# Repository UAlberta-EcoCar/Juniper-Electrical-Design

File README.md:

# Juniper-Electrical-Design - Wiper Board

The Wiper Board drives the windshield wiper on Juniper, the 2026-2027 EcoCar Urban Concept car. Shell Eco-marathon rules (2027 Chapter I, Art. 52) require Urban Concept cars to run in light rain, with an electric wiper like a production car's, worked by its own switch within easy reach of the driver. The board runs a 12 V self-parking wiper motor, reads the driver's dash switch and the park sensors, and reports its status over CAN FD. This branch contains the Rev1 board as built, the Rev2 schematic in progress, and the STM32 firmware.

Board Requirements:

- Drive a 12 V wiper motor (about 30 W) with a hardware current limit (set to about 3.5 A)
- Dedicated driver wiper switch input (off / slow / fast) on a harness connector
- Hall-sensor inputs for wiper park and end-of-sweep detection
- Reverse-polarity and transient protection on the 12 V input
- CAN FD for commands and status
- RGB status LEDs (WS2812B) and an optional OLED debug display
- USB-C and SWD for programming and debugging
- Low idle power, since all electrical energy counts on the joulemeter

MCU Chosen: STM32G491KEU6 (UFQFPN32)

- Chosen for its FDCAN controller, timers and ADCs in a small package, and the team's experience with the STM32G4 family.

Motor Driver: STMicroelectronics STSPIN948 (VFQFPN48)

- Dual full-bridge, 4.5 A rms per bridge, up to 58 V, with built-in current-sense amplifiers, an adjustable current limiter and overcurrent, thermal and undervoltage protection. The design follows ST's [EVSPIN948](https://www.st.com/en/evaluation-tools/evspin948.html) evaluation board. Bridge A drives the wiper motor; bridge B is a spare.

# Repository Structure

| Folder | Contents |
|---|---|
| `Hardware/Rev1/` | Rev1 board as built: KiCad 9 schematic, PCB, BOM and production files |
| `Hardware/Rev2/` | Rev2 schematic (work in progress) |
| `firmware/` | STM32CubeIDE project and CubeMX configuration (`Wiper-Board-Firmwire.ioc`); Rev2 configuration in `v2Firmwire/` |

# Getting Started

Clone the repository:

```sh
git clone --recursive https://github.com/UAlberta-EcoCar/Juniper-Electrical-Design.git
```

Switch to this branch:

```sh
git checkout Wiper-Board
```

Open `Hardware/Rev2/defogger_and_wiper.kicad_pro` in KiCad 9. The schematic uses a 25 mil grid; set the connection grid and the wire grid override to 25 mil.

Open `firmware/` as an existing project in STM32CubeIDE to build and flash the firmware.

# Rev2 Pin Map

| Pin | Function |
|---|---|
| PA6 / PA7 | PWM1A / PWM1B to the driver (TIM16_CH1 / TIM17_CH1) |
| PA8 / PA9 | PHA / PHB (direction) |
| PB4 / PB3 | EN/nFAULT A / B (open-drain, 39 k pull-up) |
| PA10 | nSTBY (100 k pull-down: driver sleeps until firmware wakes it) |
| PA3 / PB0 | Motor current A / B (0.5 V/A) |
| PA4 / PA5 | Wiper switch inputs BTN1 / BTN2 (dash connector J9 and on-board buttons) |
| PA0 / PA2 | Hall park sensors (J7) |
| PB5 / PB6 | FDCAN2 RX / TX |
| PA15 / PB7 | I2C1 SCL / SDA (OLED) |
| PB8 | WS2812B data (TIM8_CH2, via 74AHCT1G125; 10 k pull-down keeps BOOT0 low) |
| PA11 / PA12 | USB |
| PA13 / PA14 | SWD |
| PF0 | 8 MHz oscillator input (HSE bypass) |

# Bring-up Notes

- Driver mode switches MODE1 / MODE2 / MODE3 = LOW / HIGH / LOW (dual independent full-bridge). Power-cycle after any change.
- Rev1 only: SCL sits on PB8 (BOOT0), so the board boots into the ST bootloader after a power cycle. Program option bytes nSWBOOT0 = 0 and nBOOT0 = 1, or run it with the debugger attached. Fixed in Rev2.
- Rev1 only: the REF dividers (5.6 k / 1 k) limit the motor to about 1 A. Rev2 uses 910 ohm (about 3.5 A).

# Status

- [x] Rev1 board built and brought up
- [ ] Rev2 schematic
- [ ] Rev2 PCB layout
- [ ] Rev2 firmware

Onboarding documentation here: [https://ualberta-ecocar.github.io/Documentation/](https://ualberta-ecocar.github.io/Documentation/)

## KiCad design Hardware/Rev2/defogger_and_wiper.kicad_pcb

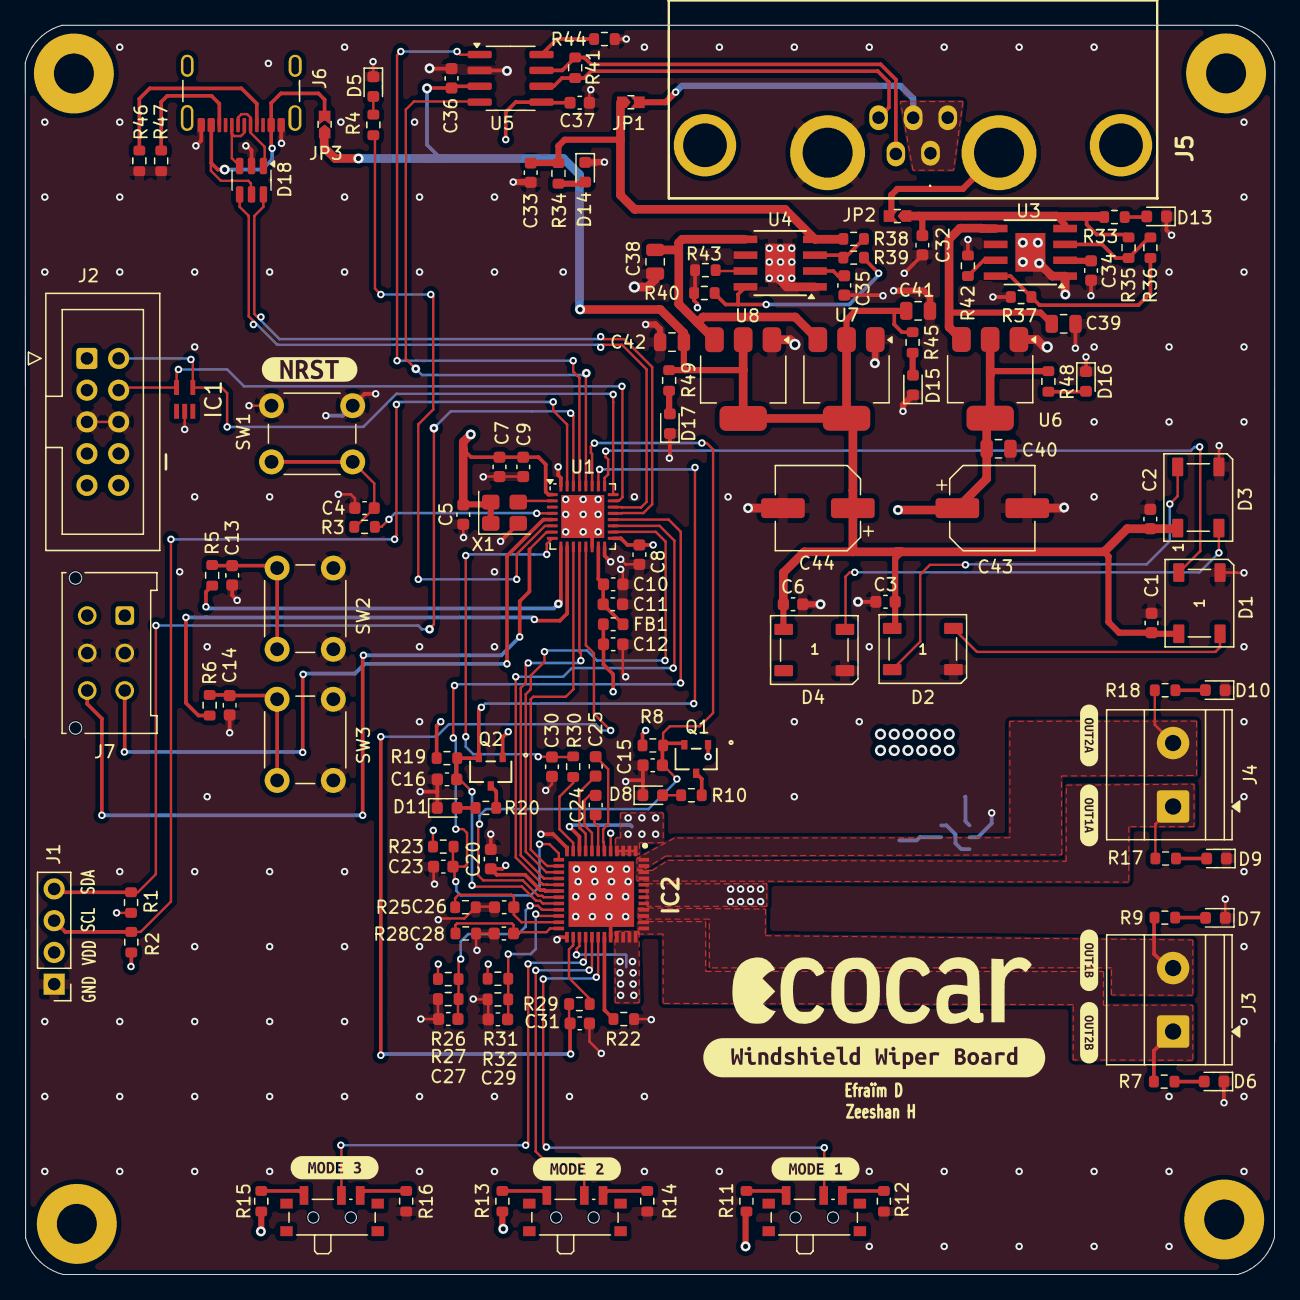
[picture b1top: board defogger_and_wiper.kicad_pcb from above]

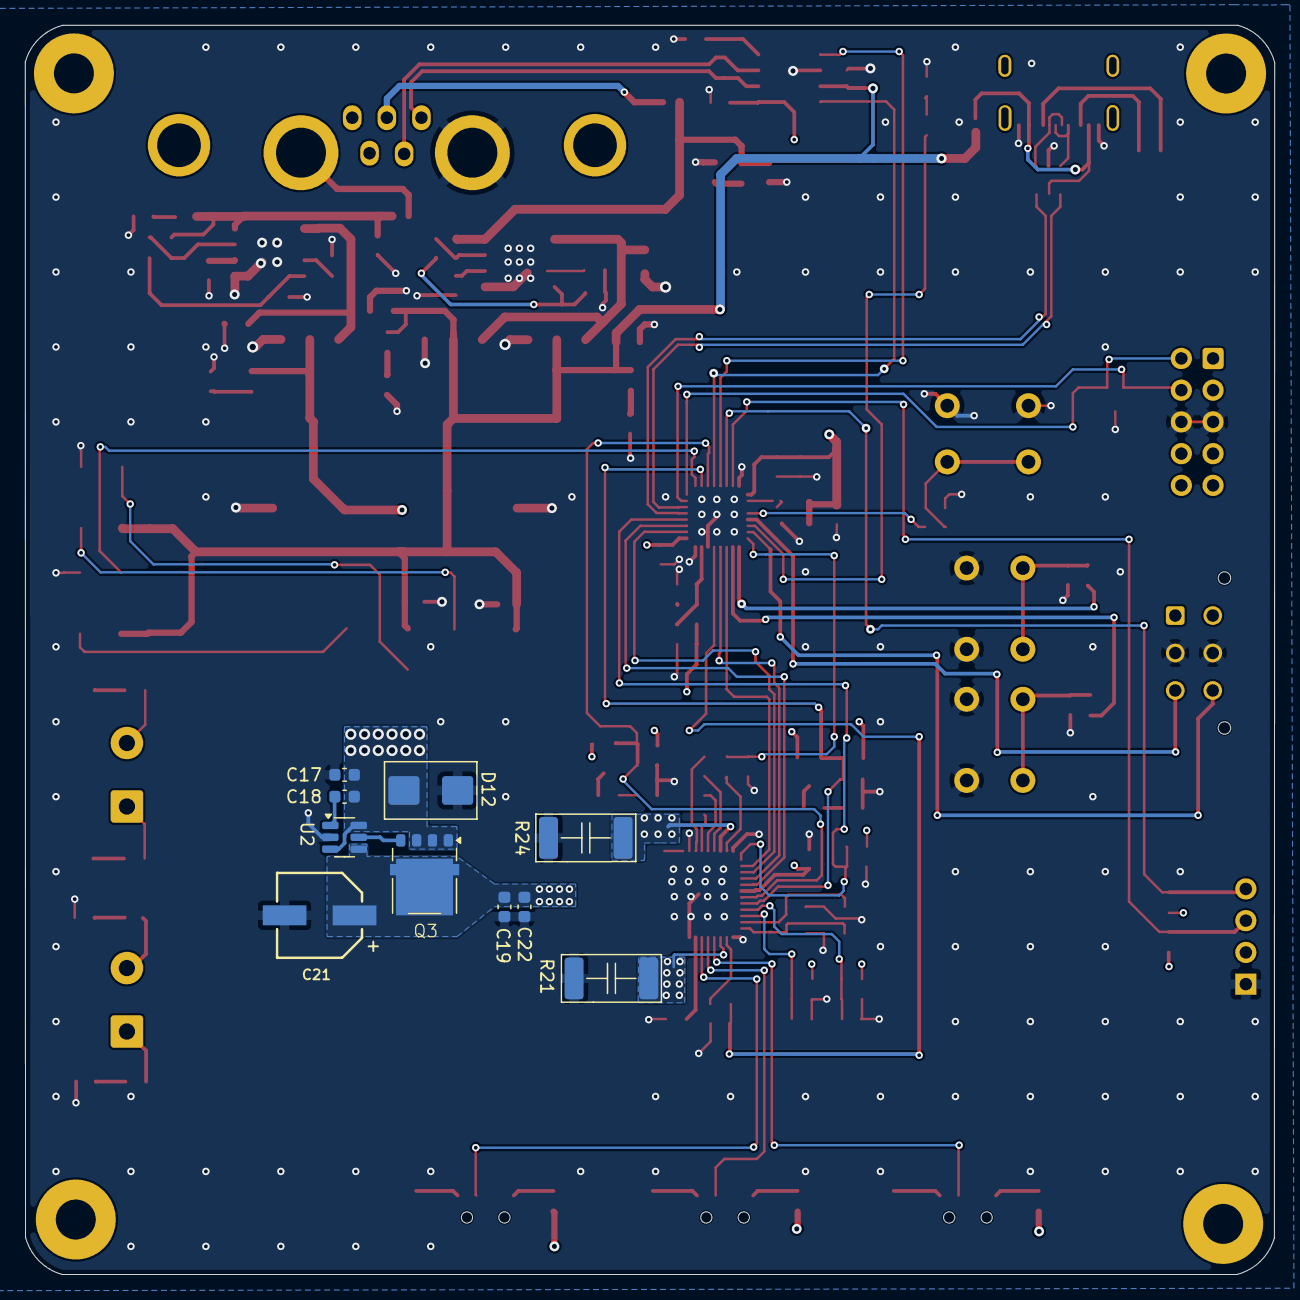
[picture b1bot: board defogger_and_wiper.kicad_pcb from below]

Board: 4 copper layers, 100.0 x 100.0 mm, 155 parts (10 on the bottom side), 100 nets.

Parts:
C1, C2, C3, C6, C10, C15, C16: 10n; C_0603_1608Metric
C4, C5, C8, C9, C13, C14, C24, C27, C29, C32, C33, C36, C37: 100n; C_0603_1608Metric
C7: 4u7; C_0603_1608Metric
C11, C12, C25: 1u; C_0603_1608Metric
C17, C19, C22: 22n; C_0603_1608Metric
C18: 0.1uF; C_0603_1608Metric
C20: 220n; C_0603_1608Metric
C21: 47u; WCAP-ASLI_6.3X5.5_DXL_
C23, C26, C28: 1n; C_0603_1608Metric
C30, C31: 100p; C_0603_1608Metric
C34, C35: 2n2; C_0603_1608Metric
C38, C39, C40, C41, C42: 10u; C_0805_2012Metric
C43, C44: 100u; CP_Elec_6.3x9.9
D1, D2, D3, D4: WS2812B; LED_WS2812B_PLCC4_5.0x5.0mm_P3.2mm
D5: GREEN; LED_0603_1608Metric
D6, D7, D9, D10, D13, D14, D15, D16, D17: BLUE; LED_0603_1608Metric
D8, D11: RED; LED_0603_1608Metric
D12: SMBJ33CA; D_SMB_TVS
D18: USBLC6-2SC6; TSOT-23-6
FB1: 600@100MHz 1A; L_0603_1608Metric
H1, H2, H3, H4: MountingHole; MountingHole_3.2mm_M3_Pad
IC1: ESDALC6V1W5; SOT65P210X110-5N
IC2: STSPIN948; QFN50P700X700X105-49N-D
J1: OLED; Display_128x64_096_I2C
J2: STM32-Prog-Header; IDC-STM32-Prog-Header_2x05_P2.54mm_Vertical
J3: MotorConnB; TerminalBlock_Phoenix_MKDS-1,5-2-5.08_1x02_P5.08mm_Horizont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
J4: MotorConnA; TerminalBlock_Phoenix_MKDS-1,5-2-5.08_1x02_P5.08mm_Horizont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
J5: Male Conn; DB7W2-Male
J6: USBC; USB_C_Receptacle_GCT_USB4105-xx-A_16P_TopMnt_Horizontal
J7: Molex_6_Pin; Molex_6_Pin_FTP
JP1: 12V Buck; J_0603_Triangular
JP2: 7V Buck; J_0603_Triangular
JP3: VBUS; J_0603_Triangular
MODE1, MODE2, MODE3: SW_SPDT; SW_SPDT_PCM12
Q1, Q2: PMOS; SOT-23_TO-236_318-AT_OSI
Q3: NTMFS4D0N08XT1G; PowerMosDFNHybrid
R1: 4k7; R_0603_1608Metric
R2: 4K7; R_0603_1608Metric
R3, R7, R9, R11, R12, R13, R14, R15, R16, R17, R18, R44: 10K; R_0603_1608Metric
R4, R36, R39, R40, R45, R48, R49: 1k; R_0603_1608Metric
R5, R6, R38: 10k; R_0603_1608Metric
R8, R19: 39K; R_0603_1608Metric
R10, R20: 330; R_0603_1608Metric
R21, R24: 50m; C_2512_6332Metric_Pad1.52x3.35mm_HandSolder
R22: 5.6K; R_0603_1608Metric
R23: 18k; R_0603_1608Metric
R25, R28: 22k; R_0603_1608Metric
R26, R31: 5.6k; R_0603_1608Metric
R27, R32: 1K; R_0603_1608Metric
R29, R30: 100; R_0603_1608Metric
R33, R34: 2k; R_0603_1608Metric
R35: 8k2; R_0603_1608Metric
R37: 1k2; R_0603_1608Metric
R41: 120R; R_0603_1608Metric
R42: 680R; R_0603_1608Metric
R43: 470R; R_0603_1608Metric
R46, R47: 5.1k; R_0603_1608Metric
SW1: RESET; SW_PUSH_6mm_H5mm
SW2: BTN1; SW_PUSH_6mm_H5mm
SW3: BTN2; SW_PUSH_6mm_H5mm
U1: STM32G491KEU6; QFN-32-1EP_5x5mm_P0.5mm_EP3.45x3.45mm
U2: LM74700; SOT-23-6
U3, U4: TPS2596; TI_SO-PowerPAD-8
U5: MCP2542FD-E/SN; SOIC-8_3.9x4.9mm_P1.27mm
U6: AZ1117IH-3.3; SOT-223-3_TabPin2
U7, U8: AZ1117-5.0; SOT-223-3_TabPin2
X1: 8Mhz; Crystal_SMD_3225-4Pin_3.2x2.5mm
kibuzzard-6A239A28: G***; kibuzzard-6A239A28
kibuzzard-6A239A38: G***; kibuzzard-6A239A38
kibuzzard-6A239A81: G***; kibuzzard-6A239A81
kibuzzard-6A239AAD: G***; kibuzzard-6A239AAD
kibuzzard-6A239ABD: G***; kibuzzard-6A239ABD
kibuzzard-6A2398C4: G***; kibuzzard-6A2398C4
kibuzzard-6A2399CD: G***; kibuzzard-6A2399CD
kibuzzard-6A2399E7: G***; kibuzzard-6A2399E7
kibuzzard-696D2580: G***; kibuzzard-696D2580

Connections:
+3.3VA: C10.1, C11.1, FB1.2, U1.15 (VDDA)
+3V3: C5.1, C7.1, C8.1, C9.1, C12.1, C20.1, C37.2, C40.1, C43.1, FB1.1, IC2.18 (VDD), J1.2, J2.7 (3.3V), J2.8 (3.3V), J7.1, J7.4, Q1.1 (D), Q2.1 (D), R1.1, R2.1, R8.1, R11.1, R13.1, R15.1, R19.1, R23.1, R26.1, R31.1, R48.1, U1.1 (VDD), U1.17 (VDD), U5.5 (VIO), U6.2 (VO), X1.1 (Tri-State), X1.4 (VDD)
+5V: C1.1, C2.1, C3.1, C6.1, C36.2, C41.1, C42.1, C44.1, D1.1 (VDD), D2.1 (VDD), D3.1 (VDD), D4.1 (VDD), JP3.1 (A), R45.1, R49.1, U5.3 (VDD), U7.2 (VO), U8.2 (VO)
+12V: C38.1, U4.5 (OUT), U7.3 (VI), U8.3 (VI)
/ADC_VA: C30.1, R30.1, U1.8 (PA3)
/ADC_VB: C31.1, R29.1, U1.13 (PB0)
/BTN1: R5.1, U1.9 (PA4)
/BTN2: R6.1, U1.10 (PA5)
/CAN AND POWER/CAN+: J5.2, R41.1, U5.7 (CANH)
/CAN AND POWER/CAN-: J5.5, R41.2, U5.6 (CANL)
/CAN AND POWER/FUSE1_IN: C33.1, JP1.1 (A), R34.1, R38.2, U4.4 (IN)
/CAN AND POWER/FUSE2_IN: C32.1, JP2.1 (A), R33.1, R35.2, U3.4 (IN)
/CAN AND POWER/FUSE2_OUT: C39.1, U3.5 (OUT), U6.3 (VI)
/CANSYNC: R4.1, U1.6 (PA1)
/CAN_RX: U1.28 (PB5), U5.4 (RXD)
/CAN_TX: U1.29 (PB6), U5.1 (TXD)
/DEBUG_SWCLK: IC1.4 (I/03), J2.2 (SWCLK), U1.24 (PA14)
/DEBUG_SWDIO: IC1.5 (I/04), J2.4 (SWDIO), U1.23 (PA13)
/DIN1: D1.2 (DOUT), D2.4 (DIN)
/DIN2: D2.2 (DOUT), D3.4 (DIN)
/DIN3: D3.2 (DOUT), D4.4 (DIN)
/HSE_OUT: U1.2 (PF0), X1.3 (OUT)
/Magnet1: J7.3, U1.5 (PA0)
/Magnet2: J7.6, U1.7 (PA2)
/Motor_driver/MODE1: IC2.30 (MODE1), MODE1.2 (B)
/Motor_driver/MODE2: IC2.29 (MODE2), MODE2.2 (B)
/Motor_driver/MODE3: IC2.28 (MODE3), MODE3.2 (B)
/Motor_driver/OUT1_A: IC2.45 (OUT1A_1), IC2.46 (OUT1A_2), J4.1, R17.1
/Motor_driver/OUT1_B: IC2.39 (OUT1B_1), IC2.40 (OUT1B_2), J3.2, R9.1
/Motor_driver/OUT2_A: IC2.47 (OUT2A_1), IC2.48 (OUT2A_2), J4.2, R18.1
/Motor_driver/OUT2_B: IC2.37 (OUT2B_1), IC2.38 (OUT2B_2), J3.1, R7.1
/Motor_driver/REFA: C27.1, IC2.21 (REFA), R26.2, R27.1
/Motor_driver/REFB: C29.1, IC2.22 (REFB), R31.2, R32.1
/Motor_driver/TOFFA: C26.2, IC2.23 (TOFFA), R25.1
/Motor_driver/TOFFB: C28.2, IC2.24 (TOFFB), R28.1
/Motor_driver/VA: IC2.11 (VA), R30.2
/Motor_driver/VB: IC2.26 (VB), R29.2
/Motor_driver/Vs12V: C19.1, C21.1, C22.1, IC2.41 (VS_1), IC2.42 (VS_2), IC2.43 (VS_3), IC2.44 (VS_4), Q3.5 (D), U2.4 (CATHODE)
/NRST: R3.1, U1.4 (PG10)
/NSTBY: C23.1, IC2.13 (NSTBY), R23.2, U1.20 (PA10)
/PHA: IC2.15 (PHA), U1.18 (PA8)
/PHB: IC2.17 (PHB), U1.19 (PA9)
/PWM1A: IC2.14 (PWM1A), U1.11 (PA6)
/PWM1B: IC2.16 (PWM1B), U1.12 (PA7)
/RGB_TIM: D1.4 (DIN), U1.25 (PA15)
/SCL: J1.3, R2.2, U1.31 (PB8)
/SDA: J1.4, R1.2, U1.30 (PB7)
/USB_D+: D18.4, U1.22 (PA12)
/USB_D-: D18.6, U1.21 (PA11)
/nFAULTA: C15.1, IC2.19 (EN/NFAULTA), Q1.2 (G), R8.2, U1.27 (PB4)
/nFAULTB: C16.1, IC2.20 (EN/NFAULTB), Q2.2 (G), R19.2, U1.26 (PB3)
GND: C1.2, C2.2, C3.2, C4.1, C5.2, C6.2, C7.2, C8.2, C9.2, C10.2, C11.2, C12.2, C13.2, C14.2, C15.2, C16.2, C17.2, C19.2, C20.2, C21.2, C22.2, C23.2, C26.1, C27.2, C28.1, C29.2, C30.2, C31.2, C32.2, C33.2, C34.2, C35.2, C36.1, C37.1, C38.2, C39.2, C40.2, C41.2, C42.2, C43.2, C44.2, D1.3 (VSS), D2.3 (VSS), D3.3 (VSS), D4.3 (VSS), D5.1 (K), D6.1 (K), D7.1 (K), D8.1 (K), D9.1 (K), D10.1 (K), D11.1 (K), D12.1 (K), D13.1 (K), D14.1 (K), D15.1 (K), D16.1 (K), D17.1 (K), D18.2, IC1.2 (GND), IC2.5 (GND_1), IC2.12 (OFFSETA), IC2.25 (OFFSETB), IC2.32 (GND_2), IC2.49 (EP), J1.1, J2.5 (GND), J2.6 (GND), J5.9, J6.A1 (GND), J6.A12 (GND), J6.B1 (GND), J6.B12 (GND), J7.2, J7.5, R12.1, R14.1, R16.1, R21.2, R22.1, R24.2, R25.2, R27.2, R28.2, R32.2, R37.2, R40.2, R42.2, R43.2, R44.2, R46.1, R47.1, SW1.1, SW2.2, SW3.2, U1.14 (VSSA), U1.16 (VSS), U1.32 (VSS), U1.33 (VSS), U2.2 (GND), U3.1 (GND), U3.9 (PAD), U4.1 (GND), U4.9 (PAD), U5.2 (VSS), U6.1 (GND), U7.1 (GND), U8.1 (GND), X1.2 (GND)
unnamed: C4.2, R3.2, SW1.2
unnamed: C13.1, R5.2, SW2.1
unnamed: C14.1, R6.2, SW3.1
unnamed: D5.2 (A), R4.2
unnamed: D6.2 (A), R7.2
unnamed: D7.2 (A), R9.2
unnamed: D8.2 (A), R10.2
unnamed: D9.2 (A), R17.2
unnamed: D10.2 (A), R18.2
unnamed: D11.2 (A), R20.2
unnamed: D13.2 (A), R33.2
unnamed: D14.2 (A), R34.2
unnamed: D15.2 (A), R45.2
unnamed: D16.2 (A), R48.2
unnamed: D17.2 (A), R49.2
unnamed: D18.1, J6.A7 (D-), J6.B7 (D-)
unnamed: D18.3, J6.A6 (D+), J6.B6 (D+)
unnamed: C24.1, IC2.7 (CP1)
unnamed: C24.2, IC2.8 (CP2)
unnamed: IC2.1 (LSS1A_1), IC2.2 (LSS1A_2), IC2.3 (LSS2A_1), IC2.4 (LSS2A_2), IC2.10 (SENSEA), R24.1
unnamed: IC2.27 (SENSEB), IC2.33 (LSS2B_1), IC2.34 (LSS2B_2), IC2.35 (LSS1B_1), IC2.36 (LSS1B_2), R21.1
unnamed: IC2.31 (SR), R22.2
unnamed: C25.1, IC2.9 (VBOOT)
unnamed: C25.2, IC2.6 (VSPUMP)
unnamed: J6.A5 (CC1), R46.2
unnamed: J6.B5 (CC2), R47.2
unnamed: MODE1.1 (A), R11.2
unnamed: MODE1.3 (C), R12.2
unnamed: MODE2.1 (A), R13.2
unnamed: MODE2.3 (C), R14.2
unnamed: MODE3.1 (A), R15.2
unnamed: MODE3.3 (C), R16.2
unnamed: Q1.3 (S), R10.1
unnamed: Q2.3 (S), R20.1
unnamed: Q3.4 (G), U2.5 (GATE)
unnamed: C18.2, U2.1 (VCAP)
unnamed: R35.1, R36.2, U3.3 (EN/UVLO)
unnamed: R42.1, U3.7 (ILM)
unnamed: R36.1, R37.1, U3.8 (OVLO)
unnamed: C34.1, U3.2 (dV/dT)
unnamed: R38.1, R39.2, U4.3 (EN/UVLO)
unnamed: R43.1, U4.7 (ILM)
unnamed: R39.1, R40.1, U4.8 (OVLO)
unnamed: C35.1, U4.2 (dV/dT)
unnamed: R44.1, U5.8 (STBY)
OUT_{7V}: J5.8, JP2.2 (B)
OUT_{12V}: C17.1, C18.1, D12.2 (A), J5.1, J5.3, J5.4, JP1.2 (B), Q3.1 (S), Q3.2 (S), Q3.3 (S), U2.3 (EN), U2.6 (ANODE)
VBUS: D18.5, J6.A4 (VBUS), J6.A9 (VBUS), J6.B4 (VBUS), J6.B9 (VBUS), JP3.2 (B)

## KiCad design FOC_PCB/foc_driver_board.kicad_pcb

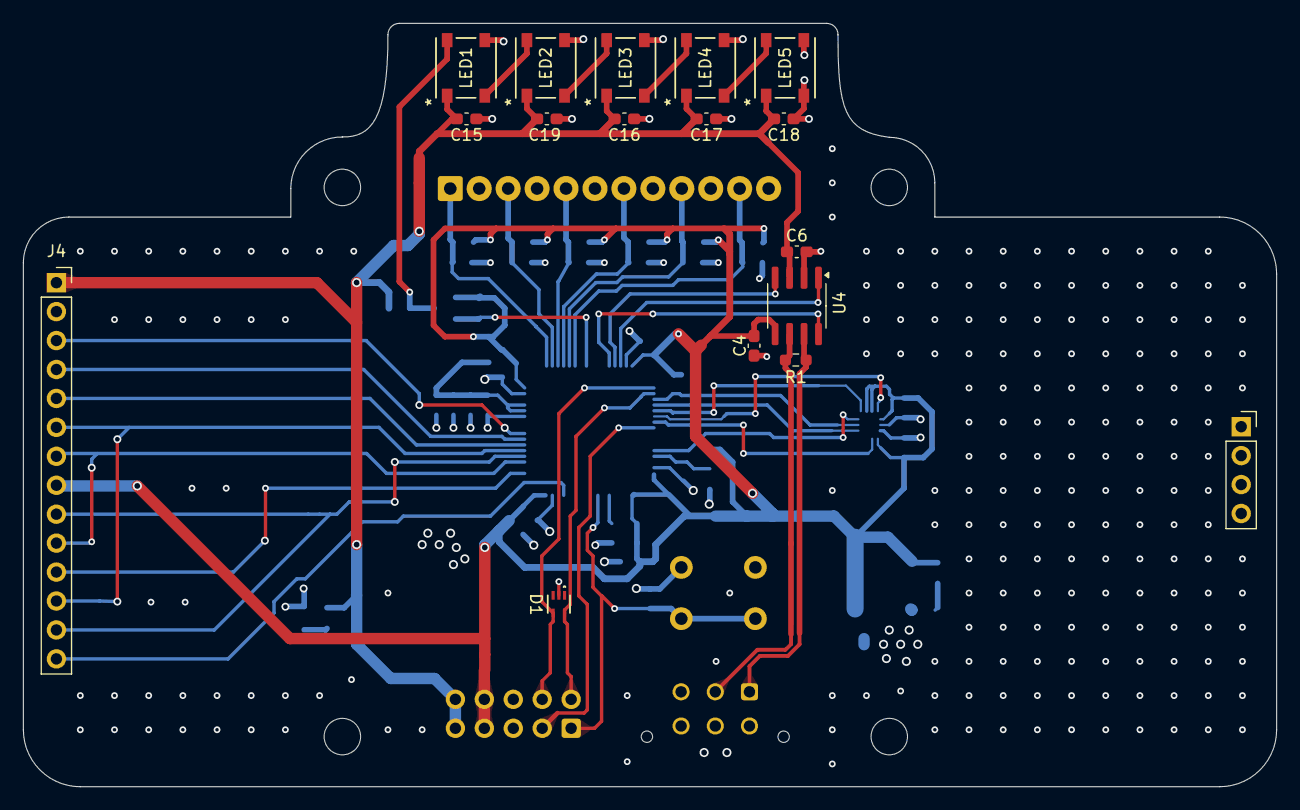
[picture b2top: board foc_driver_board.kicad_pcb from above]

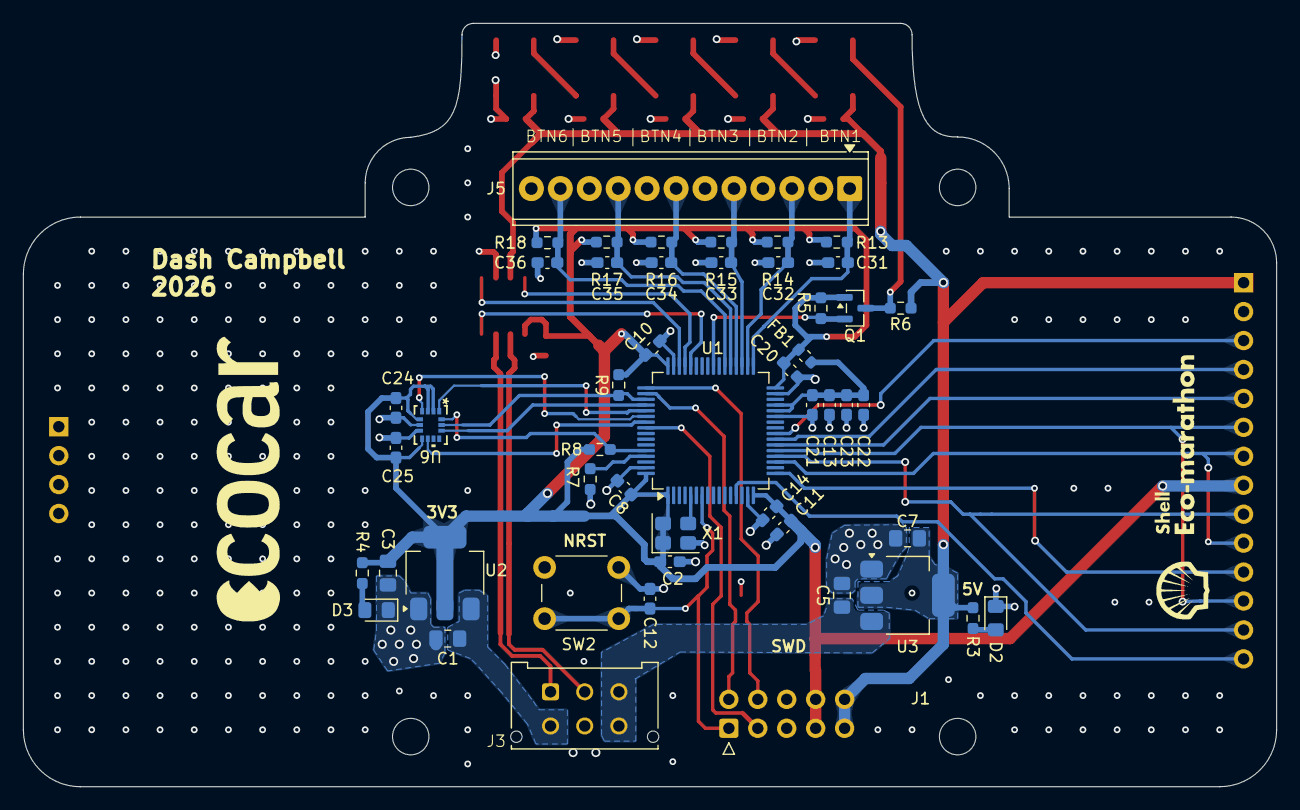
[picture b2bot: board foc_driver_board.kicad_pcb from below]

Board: 4 copper layers, 110.0 x 67.0 mm, 69 parts (49 on the bottom side), 45 nets.

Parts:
C1, C5: 10u; C_0805_2012Metric_Pad1.18x1.45mm_HandSolder
C2, C4, C8, C10, C12, C14, C15, C16, C17, C18, C19, C20, C21, C22, C24, C25, C31, C32, C33, C34, C35, C36: 0u1; C_0603_1608Metric_Pad1.08x0.95mm_HandSolder
C3, C7: 22u; C_0805_2012Metric_Pad1.18x1.45mm_HandSolder
C6, C13, C23: 1u; C_0603_1608Metric_Pad1.08x0.95mm_HandSolder
C11: 4u7; C_0603_1608Metric_Pad1.08x0.95mm_HandSolder
D1: ESDALC6V1P5
D2, D3: LED; LED_0805_2012Metric_Pad1.15x1.40mm_HandSolder
FB1: FerriteBead; L_0603_1608Metric
H1, H2, H3, H4: MountingHole; MountingHole_3.2mm_M3
J1: STM32-Prog-Header; IDC-STM32-Prog-Header_2x05_P2.54mm_Vertical
J3: Conn_01x06_Pin; STD_PWR_HEADER
J4: ST7796 DIsplay; ILI9488
J5: Conn_01x12_Socket; TerminalBlock_Phoenix_MPT-0,5-12-2.54_1x12_P2.54mm_Horizont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
LED1, LED2, LED3, LED4, LED5: COM-16347; COM-16347_SPK
Q1: BSS138; SOT-23
R1: 120R; R_0603_1608Metric_Pad0.98x0.95mm_HandSolder
R3, R4: 4k7; R_0603_1608Metric_Pad0.98x0.95mm_HandSolder
R5, R6, R7, R8, R9, R13, R14, R15, R16, R17, R18: 10k; R_0603_1608Metric_Pad0.98x0.95mm_HandSolder
SW2: SW_Push; SW_PUSH_6mm
U1: STM32G491RET6; LQFP-64_10x10mm_P0.5mm
U2: AZ1117IH-3.3; SOT-223-3_TabPin2
U3: AZ1117IH-5.0; SOT-223-3_TabPin2
U4: MCP2542FD; SOIC-8_3.9x4.9mm_P1.27mm
U6: LSM6DSO32TR; LGA-14L_2P5X3X0P83_STM
X1: OXETDLJANF-8MHZ; Crystal_SMD_3225-4Pin_3.2x2.5mm

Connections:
+3.3VA: C13.1, C21.1, C22.1, C23.1, FB1.2, U1.28 (VREF+), U1.29 (VDDA)
+3V3: C2.1, C3.1, C4.1, C8.1, C10.1, C11.1, C14.1, C20.1, C24.1, C25.1, FB1.1, J1.7 (3.3V), J1.8 (3.3V), J4.8, Q1.1 (G), R4.1, R5.1, R8.1, R9.1, R13.1, R14.1, R15.1, R16.1, R17.1, R18.1, U1.1 (VBAT), U1.16 (VDD), U1.32 (VDD), U1.48 (VDD), U1.64 (VDD), U2.2 (VO), U4.5 (VIO), U6.2 (SDx), U6.3 (SCx), U6.5 (VDDIO), U6.8 (VDD), X1.1 (Tri-State), X1.4 (VDD)
+5V: C6.1, C7.1, C15.1, C16.1, C17.1, C18.1, C19.1, J1.9 (5V), J1.10 (5V), J4.1, LED1.1 (VDD), LED2.1 (VDD), LED3.1 (VDD), LED4.1 (VDD), LED5.1 (VDD), R3.1, R6.1, U3.2 (VO), U4.3 (VDD)
+7V: C1.1, J3.4, U2.3 (VI)
+12V: C5.1, J3.3, J3.6, U3.3 (VI)
/foc_driver_board/3V3_LED: D3.2 (A), R4.2
/foc_driver_board/5V_LED: D2.2 (A), R3.2
/foc_driver_board/DIN1: LED1.4 (DIN), Q1.3 (D), R6.2
/foc_driver_board/DIN2: LED1.2 (DOUT), LED2.4 (DIN)
/foc_driver_board/DIN3: LED2.2 (DOUT), LED3.4 (DIN)
/foc_driver_board/DIN4: LED3.2 (DOUT), LED4.4 (DIN)
/foc_driver_board/DIN5: LED4.2 (DOUT), LED5.4 (DIN)
/foc_driver_board/FDCAN+: J3.1, R1.2, U4.7 (CANH)
/foc_driver_board/FDCAN-: J3.2, R1.1, U4.6 (CANL)
/mcu/BOOT0: R7.1, U1.61 (PB8)
BTN1: C31.1, J5.1, R13.2, U1.33 (PB11)
BTN2: C32.1, J5.3, R14.2, U1.34 (PB12)
BTN3: C33.1, J5.5, R15.2, U1.35 (PB13)
BTN4: C34.1, J5.7, R16.2, U1.36 (PB14)
BTN5: C35.1, J5.9, R17.2, U1.37 (PB15)
BTN6: C36.1, J5.11, R18.2, U1.38 (PC6)
FDCAN_RX: U1.45 (PA11), U4.4 (RXD)
FDCAN_STBY: U1.44 (PA10), U4.8 (STBY)
FDCAN_TX: U1.46 (PA12), U4.1 (TXD)
GNDA: C1.2, C2.2, C3.2, C4.2, C5.2, C6.2, C7.2, C8.2, C10.2, C11.2, C12.2, C13.2, C14.2, C15.2, C16.2, C17.2, C18.2, C19.2, C20.2, C21.2, C22.2, C23.2, C24.2, C25.2, C31.2, C32.2, C33.2, C34.2, C35.2, C36.2, D1.2, D2.1 (K), D3.1 (K), J1.5 (GND), J1.6 (GND), J3.5, J4.2, J5.2, J5.4, J5.6, J5.8, J5.10, J5.12, LED1.3 (VSS), LED2.3 (VSS), LED3.3 (VSS), LED4.3 (VSS), LED5.2 (DOUT), LED5.3 (VSS), R7.2, SW2.1, U1.15 (VSS), U1.27 (VSSA), U1.31 (VSS), U1.47 (VSS), U1.63 (VSS), U2.1 (GND), U3.1 (GND), U4.2 (VSS), U6.6 (GND), U6.7 (GND), X1.2 (GND)
IMU_CS: U1.52 (PC10), U6.12 (CS)
IMU_INT1: U1.54 (PC12), U6.4 (INT1)
IMU_INT2: U1.55 (PD2), U6.9 (INT2)
IMU_SA0: U1.53 (PC11), U6.1 (SDO/SA0)
IMU_SCL: R9.2, U1.51 (PA15), U6.13 (SCL)
IMU_SDA: R8.2, U1.60 (PB7), U6.14 (SDA)
LCD_CS: J4.3, U1.24 (PB0)
LCD_DC: J4.5, U1.22 (PC4)
LCD_RESET: J4.4, U1.23 (PC5)
LED_IN: Q1.2 (S), R5.2, U1.40 (PC8)
NRST: C12.1, J1.1 (RST), SW2.2, U1.7 (PG10)
RCC: U1.5 (PF0), X1.3 (OUT)
SPI_MISO: J4.9, J4.13, U1.20 (PA6)
SPI_MOSI: J4.6, J4.12, U1.21 (PA7)
SPI_SCK: J4.7, J4.10, U1.19 (PA5)
SWCLK: D1.5, J1.2 (SWCLK), U1.50 (PA14)
SWDIO: D1.4, J1.4 (SWDIO), U1.49 (PA13)
SWO: J1.3 (SWIM), U1.56 (PB3)
T_CS: J4.11, U1.17 (PA3)
T_IRQ: J4.14, U1.13 (PA1)

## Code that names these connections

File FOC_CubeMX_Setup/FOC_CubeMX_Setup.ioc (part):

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Mcu.Name=STM32G491R(C-E)Tx
Mcu.Package=LQFP64
Mcu.UserName=STM32G491RETx
PA1.GPIOParameters=GPIO_Label
PA1.GPIO_Label=T_IRQ
PA1.Signal=GPXTI1
PA10.GPIOParameters=GPIO_Label
PA10.GPIO_Label=FDCAN_STBY
PA10.Signal=GPIO_Output
PA11.GPIOParameters=GPIO_PuPd
PA11.GPIO_PuPd=GPIO_PULLUP
PA11.Mode=FDCAN_Activate
PA11.Signal=FDCAN1_RX
PA12.Mode=FDCAN_Activate
PA12.Signal=FDCAN1_TX
PA13.Mode=Trace_Asynchronous_SW
PA13.Signal=SYS_JTMS-SWDIO
PA14.Mode=Trace_Asynchronous_SW
PA14.Signal=SYS_JTCK-SWCLK
PA15.GPIOParameters=GPIO_Label
PA15.GPIO_Label=IMU_SCL
PA15.Mode=I2C
PA15.Signal=I2C1_SCL
PA3.GPIOParameters=GPIO_Label
PA3.GPIO_Label=T_CS
PA3.Signal=GPIO_Output
PA4.GPIOParameters=GPIO_Label
PA4.GPIO_Label=LCD_BRIGHT
PA4.Signal=GPIO_Output
PA5.Mode=Full_Duplex_Master
PA5.Signal=SPI1_SCK
PA6.Mode=Full_Duplex_Master
PA6.Signal=SPI1_MISO
PA7.Mode=Full_Duplex_Master
PA7.Signal=SPI1_MOSI
PB0.GPIOParameters=GPIO_Label
PB0.GPIO_Label=LCD_CS
PB0.Signal=GPIO_Output
PB11.GPIOParameters=GPIO_Label
PB11.GPIO_Label=BTN1
PB11.Signal=GPXTI11
PB12.GPIOParameters=GPIO_Label
PB12.GPIO_Label=BTN2
PB12.Signal=GPXTI12
PB13.GPIOParameters=GPIO_Label
PB13.GPIO_Label=BTN3
PB13.Signal=GPXTI13
PB14.GPIOParameters=GPIO_Label
PB14.GPIO_Label=BTN4
PB14.Signal=GPXTI14
PB15.GPIOParameters=GPIO_Label
PB15.GPIO_Label=BTN5
PB15.Signal=GPXTI15
PB3.Mode=Trace_Asynchronous_SW
PB3.Signal=SYS_JTDO-SWO
PB7.GPIOParameters=GPIO_Label
PB7.GPIO_Label=IMU_SDA
PB7.Mode=I2C
PB7.Signal=I2C1_SDA
PC10.GPIOParameters=GPIO_Label
PC10.GPIO_Label=IMU_CS
PC10.Signal=GPIO_Output
PC11.GPIOParameters=GPIO_Label
PC11.GPIO_Label=IMU_SA0
PC11.Signal=GPIO_Output
PC4.GPIOParameters=GPIO_Label
PC4.GPIO_Label=LCD_DC
PC4.Signal=GPIO_Output
PC5.GPIOParameters=GPIO_Label
PC5.GPIO_Label=LCD_RESET
PC5.Signal=GPIO_Output
PC6.GPIOParameters=GPIO_Label
PC6.GPIO_Label=BTN6
PC6.Signal=GPXTI6
PC8.GPIOParameters=GPIO_Label
PC8.GPIO_Label=LED_IN
PC8.Signal=S_TIM3_CH3
PD2.GPIOParameters=GPIO_Label
PD2.GPIO_Label=IMU_INT2
PD2.Signal=GPXTI2
PF0-OSC_IN.Mode=HSE-External-Clock-Source
PF0-OSC_IN.Signal=RCC_OSC_IN
RCC.HSE_VALUE=8000000
RCC.SYSCLKFreq_VALUE=170000000
RCC.SYSCLKSource=RCC_SYSCLKSOURCE_PLLCLK
board=custom

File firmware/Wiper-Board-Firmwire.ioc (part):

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Mcu.Name=STM32G491K(C-E)Ux
Mcu.Package=UFQFPN32
Mcu.UserName=STM32G491KEUx
PA0.GPIOParameters=GPIO_Label
PA0.GPIO_Label=Magnet1
PA0.Signal=GPIO_Input
PA1.GPIOParameters=GPIO_Label
PA1.GPIO_Label=CAN_SYNC
PA1.Signal=GPIO_Output
PA10.GPIOParameters=GPIO_Label
PA10.GPIO_Label=NSTBY
PA10.Signal=GPIO_Output
PA11.Mode=Device
PA11.Signal=USB_DM
PA12.Mode=Device
PA12.Signal=USB_DP
PA13.Signal=SYS_JTMS-SWDIO
PA14.Signal=SYS_JTCK-SWCLK
PA15.GPIOParameters=GPIO_Label
PA15.GPIO_Label=RGB_LED_PWM
PA15.Signal=S_TIM8_CH1
PA2.GPIOParameters=GPIO_Label
PA2.GPIO_Label=Magnet2
PA2.Signal=GPIO_Input
PA3.GPIOParameters=GPIO_Label
PA3.GPIO_Label=ADC_VA
PA3.Mode=IN4-Single-Ended
PA3.Signal=ADC1_IN4
PA4.GPIOParameters=GPIO_PuPd,GPIO_Label
PA4.GPIO_Label=BTNA
PA4.GPIO_PuPd=GPIO_PULLUP
PA4.Signal=GPIO_Input
PA5.GPIOParameters=GPIO_PuPd,GPIO_Label
PA5.GPIO_Label=BTNB
PA5.GPIO_PuPd=GPIO_PULLUP
PA5.Signal=GPIO_Input
PA6.GPIOParameters=GPIO_Label
PA6.GPIO_Label=PWM1A
PA6.Signal=S_TIM16_CH1
PA7.GPIOParameters=GPIO_Label
PA7.GPIO_Label=PWM1B
PA7.Signal=S_TIM17_CH1
PA8.GPIOParameters=GPIO_Label
PA8.GPIO_Label=PHA
PA8.Signal=GPIO_Output
PA9.GPIOParameters=GPIO_Label
PA9.GPIO_Label=PHB
PA9.Signal=GPIO_Output
PB0.GPIOParameters=GPIO_Label
PB0.GPIO_Label=ADC_VB
PB0.Mode=IN15-Single-Ended
PB0.Signal=ADC1_IN15
PB3.GPIOParameters=GPIO_Label,GPIO_ModeDefaultOutputPP
PB3.GPIO_Label=ENB
PB3.GPIO_ModeDefaultOutputPP=GPIO_MODE_OUTPUT_OD
PB3.Signal=GPIO_Output
PB4.GPIOParameters=GPIO_Label,GPIO_ModeDefaultOutputPP
PB4.GPIO_Label=ENA
PB4.GPIO_ModeDefaultOutputPP=GPIO_MODE_OUTPUT_OD
PB4.Signal=GPIO_Output
PB5.Mode=FDCAN_Activate
PB5.Signal=FDCAN2_RX
PB6.Mode=FDCAN_Activate
PB6.Signal=FDCAN2_TX
PB7.GPIOParameters=GPIO_Label
PB7.GPIO_Label=OLED_SDA
PB7.Mode=I2C
PB7.Signal=I2C1_SDA
PB8-BOOT0.GPIOParameters=GPIO_Label
PB8-BOOT0.GPIO_Label=OLED_SCL
PB8-BOOT0.Mode=I2C
PB8-BOOT0.Signal=I2C1_SCL
PF0-OSC_IN.Mode=HSE-External-Oscillator
PF0-OSC_IN.Signal=RCC_OSC_IN
PF1-OSC_OUT.Mode=HSE-External-Oscillator
PF1-OSC_OUT.Signal=RCC_OSC_OUT
RCC.HSE_VALUE=8000000
RCC.SYSCLKFreq_VALUE=16000000
board=custom

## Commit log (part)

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2026-06-06 Update README with project details and setup instructions
    Expanded project description and added onboarding instructions.
